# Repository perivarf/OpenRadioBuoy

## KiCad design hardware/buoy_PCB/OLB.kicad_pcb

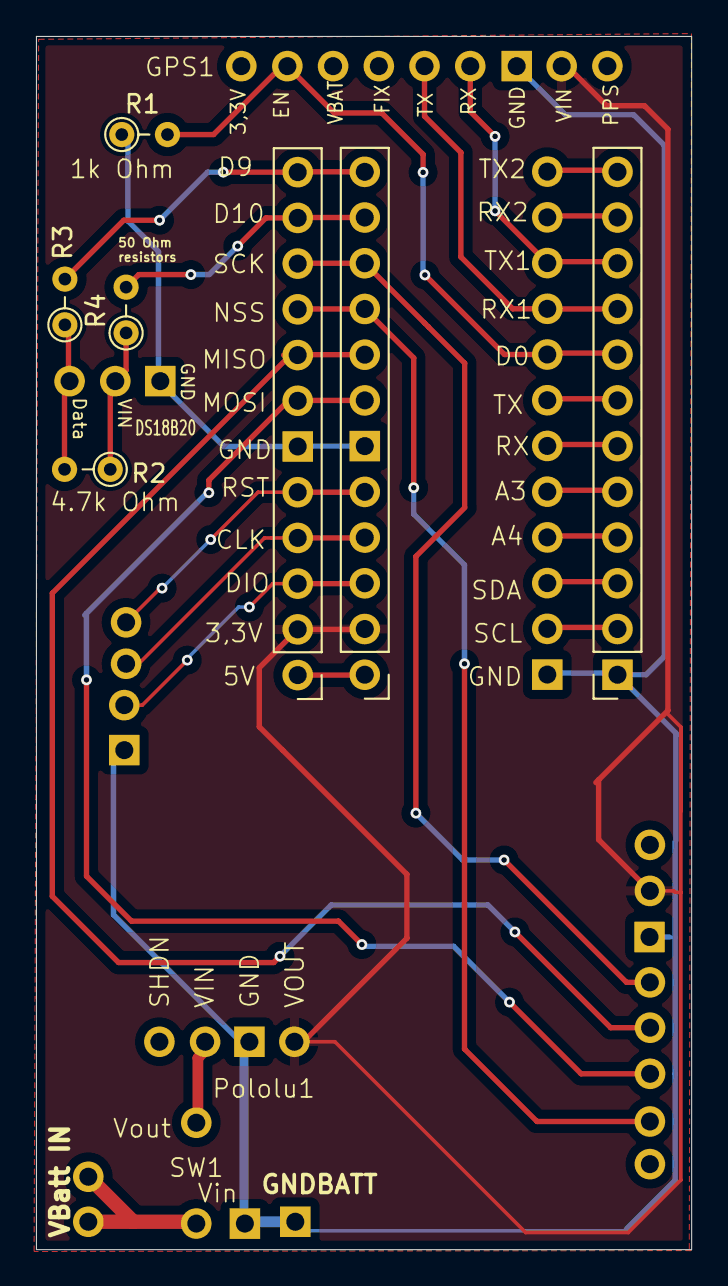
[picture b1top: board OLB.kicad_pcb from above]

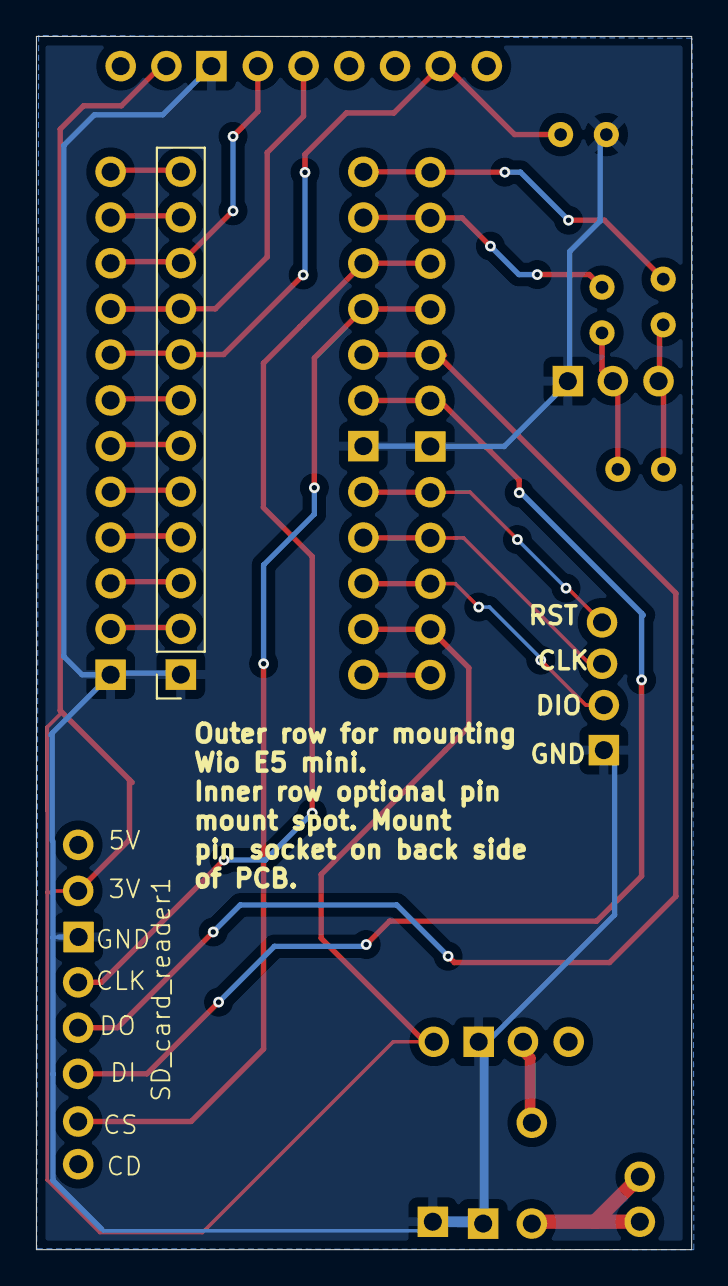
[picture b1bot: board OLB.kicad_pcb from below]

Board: 2 copper layers, 36.4 x 67.4 mm, 11 parts (2 on the bottom side), 14 nets.

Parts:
DS18B20: DS18B20
GPS1: GPS
Pololu1: Pololu3,3V
R1: 1k Ohm; R_Axial_DIN0204_L3.6mm_D1.6mm_P2.54mm_Vertical
R2: 4.7k Ohm; R_Axial_DIN0204_L3.6mm_D1.6mm_P2.54mm_Vertical
R3, R4: 50 Ohm; R_Axial_DIN0204_L3.6mm_D1.6mm_P2.54mm_Vertical
RHS Wio pins: PinSocket_1x12_P2.54mm_Vertical
SD_card_reader1: 254; SD_writer
SW1: SW_Reed; ReedSwitch
Wio1: WIO_E5_THT

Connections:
GND: DS18B20.Gn (GND), GPS1.Gn (GND), Pololu1.Gn (GND), R1.1, RHS Wio pins.1, SD_card_reader1.Gn (GND), Wio1.Gn (GND)
unnamed: DS18B20.TD (D), R2.2, R3.1
unnamed: DS18B20.TV (Vin), R2.1, R4.1
unnamed: GPS1.2G (EN), R1.2, RHS Wio pins.8, Wio1.D0
unnamed: GPS1.6G (RX), RHS Wio pins.10, Wio1.TX1
unnamed: GPS1.5G (TX), RHS Wio pins.9, Wio1.RX1
unnamed: GPS1.3V (VIN), Pololu1.3V (Vout), SD_card_reader1.3V, Wio1.3V (3,3V)
unnamed: Pololu1.Pin (Vin), SW1.1
unnamed: R3.2, Wio1.D9
unnamed: R4.2, Wio1.D10
unnamed: SD_card_reader1.SDCL (CLK), Wio1.A1 (SCK)
unnamed: SD_card_reader1.SDCS (CS), Wio1.NSS
unnamed: SD_card_reader1.SDDI (DI), Wio1.A5 (MOSI)
unnamed: SD_card_reader1.SDDO (DO), Wio1.A6 (MISO)
